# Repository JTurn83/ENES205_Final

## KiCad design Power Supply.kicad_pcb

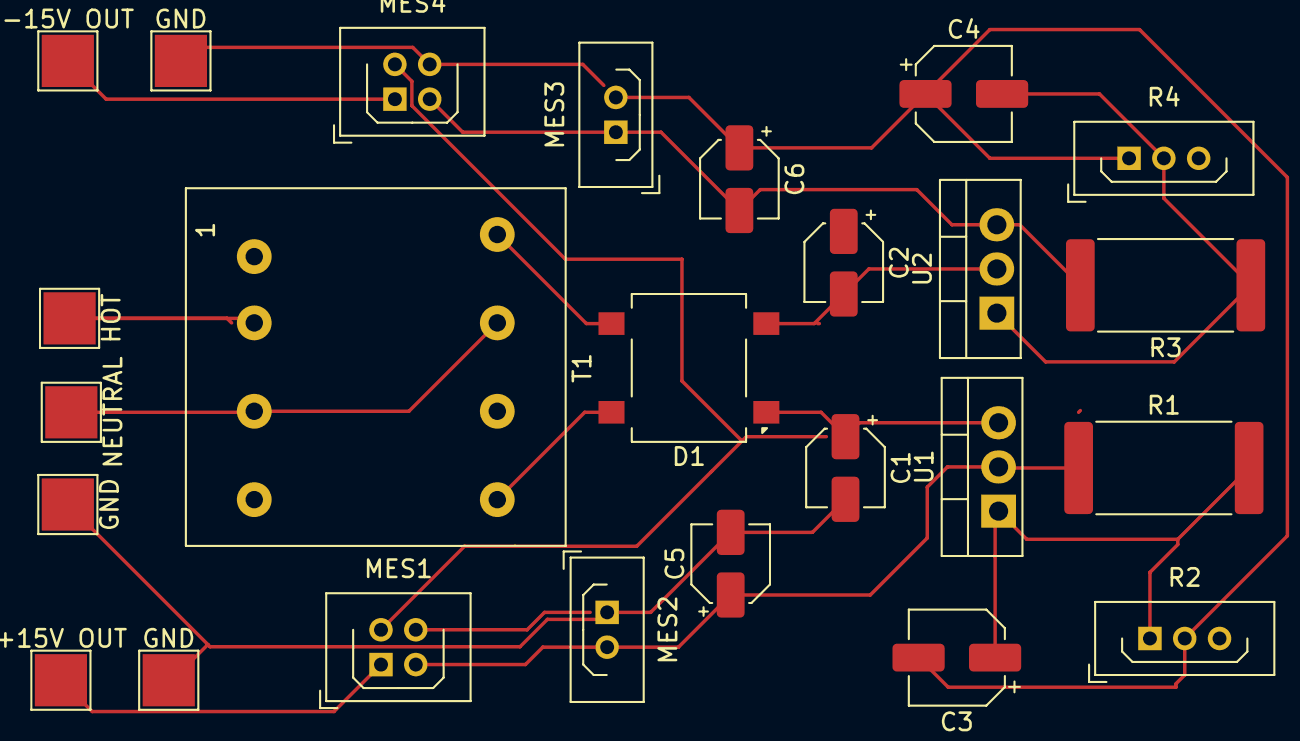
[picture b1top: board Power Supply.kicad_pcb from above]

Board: 2 copper layers, 25 parts (0 on the bottom side), 12 nets.

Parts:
+15V OUT: +15V Out; TestPoint_Pad_3.0x3.0mm
-15V OUT: -15V Out; TestPoint_Pad_3.0x3.0mm
C1, C2: 0.1μF; CP_Elec_4x4.5
C3, C4: 10μF; CP_Elec_5x5.3
C5, C6: 1μF; CP_Elec_4x5.8
D1: CD-HD2004; Diode_Bridge_OnSemi_SDIP-4L
GND: GND; TestPoint_Pad_3.0x3.0mm
GND#2, GND#3: GND; TestPoint_Pad_3.0x3.0mm
HOT: HOT; TestPoint_Pad_3.0x3.0mm
MES1, MES4: Adafruit Ammeter; Harwin_LTek-Male_2x02_P2.00mm_Vertical
MES2, MES3: Adafruit Voltmeter; Harwin_LTek-Male_02_P2.00mm_Vertical
NEUTRAL: NEUTRAL; TestPoint_Pad_3.0x3.0mm
R1, R3: 120Ω 1%; R_4020_10251Metric_Pad1.65x5.30mm_HandSolder
R2, R4: 2kΩ; Harwin_LTek-Male_03_P2.00mm_Vertical
T1: Triad F5-24; Transformer_Coilcraft_Q4434-B_Rhombus-T1311
U1: LM317_TO-220; TO-220-3_Vertical
U2: LM337_TO220; TO-220-3_Vertical

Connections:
/1.25 TO 21.35V Output: +15V OUT.4, MES1.1 (-)
/-1.25 TO -21.35V Output: -15V OUT.6, MES4.1 (-)
GND: C1.2, C2.1, C3.2, C4.1, C5.2, C6.1, GND.7, GND#2.5, GND#3.3, MES2.1 (-), MES3.2 (+), MES4.4, NEUTRAL.2, R2.2, R4.1, T1.3 (AB), T1.7 (SC)
unnamed: C1.1, D1.1 (+), U1.3 (VI)
unnamed: C2.2, D1.2 (-), U2.2 (VI)
unnamed: C5.1, MES1.2 (+), MES2.2 (+), R1.1, U1.2 (VO)
unnamed: C6.2, MES3.1 (-), MES4.2 (+), R3.2, U2.3 (VO)
unnamed: HOT.1, T1.2 (AA)
unnamed: D1.3, T1.8 (SA)
unnamed: D1.4, T1.5 (SB)
unnamed: C3.1, R1.2, R2.1, U1.1 (ADJ)
unnamed: C4.2, R3.1, R4.2, U2.1 (ADJ)

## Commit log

2025-05-14 Add files via upload
    KiCad Schematic and PCB files
2025-05-14 Add files via upload
    Datasheets for selected parts
